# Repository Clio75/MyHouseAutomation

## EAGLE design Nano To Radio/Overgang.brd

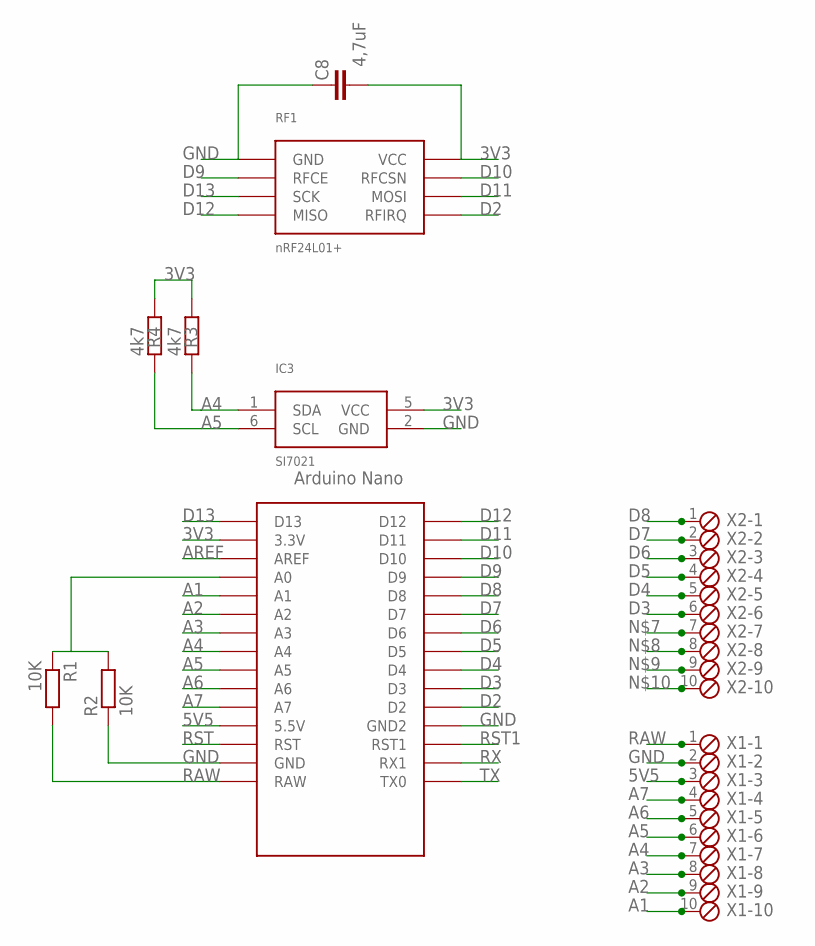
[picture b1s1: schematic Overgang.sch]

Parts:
C8: 4,7uF; C1206K
IC3: SI7021; DFN6
R1, R2: 10K; R0805
R3, R4: 4k7; R0805
RF1: nRF24L01+; 2X4-2.54MM
U$1: NANO
X1, X2: MPT10; 10POL254

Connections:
3V3: C8.1, IC3.5 (VCC), R3.1, R4.1, RF1.P$2 (VCC), U$1.3.3V
5V5: U$1.5V (5.5V), X1.3
A1: U$1.A1, X1.10
A2: U$1.A2, X1.9
A3: U$1.A3, X1.8
A4: IC3.1 (SDA), R3.2, U$1.A4, X1.7
A5: IC3.6 (SCL), R4.2, U$1.A5, X1.6
A6: U$1.A6, X1.5
A7: U$1.A7, X1.4
AREF: U$1.AREF
D2: RF1.P$8 (RFIRQ), U$1.D2
D3: U$1.D3, X2.6
D4: U$1.D4, X2.5
D5: U$1.D5, X2.4
D6: U$1.D6, X2.3
D7: U$1.D7, X2.2
D8: U$1.D8, X2.1
D9: RF1.P$3 (RFCE), U$1.D9
D10: RF1.P$4 (RFCSN), U$1.D10
D11: RF1.P$6 (MOSI), U$1.D11
D12: RF1.P$7 (MISO), U$1.D12
D13: RF1.P$5 (SCK), U$1.D13
GND: C8.2, IC3.2 (GND), R2.1, RF1.P$1 (GND), U$1.GND, U$1.GND1 (GND2), X1.2
unnamed: R1.1, R2.2, U$1.A0
RAW: R1.2, U$1.RAW, X1.1
RST: U$1.RST
RST1: U$1.RST1
RX: U$1.RX1
TX: U$1.TX0

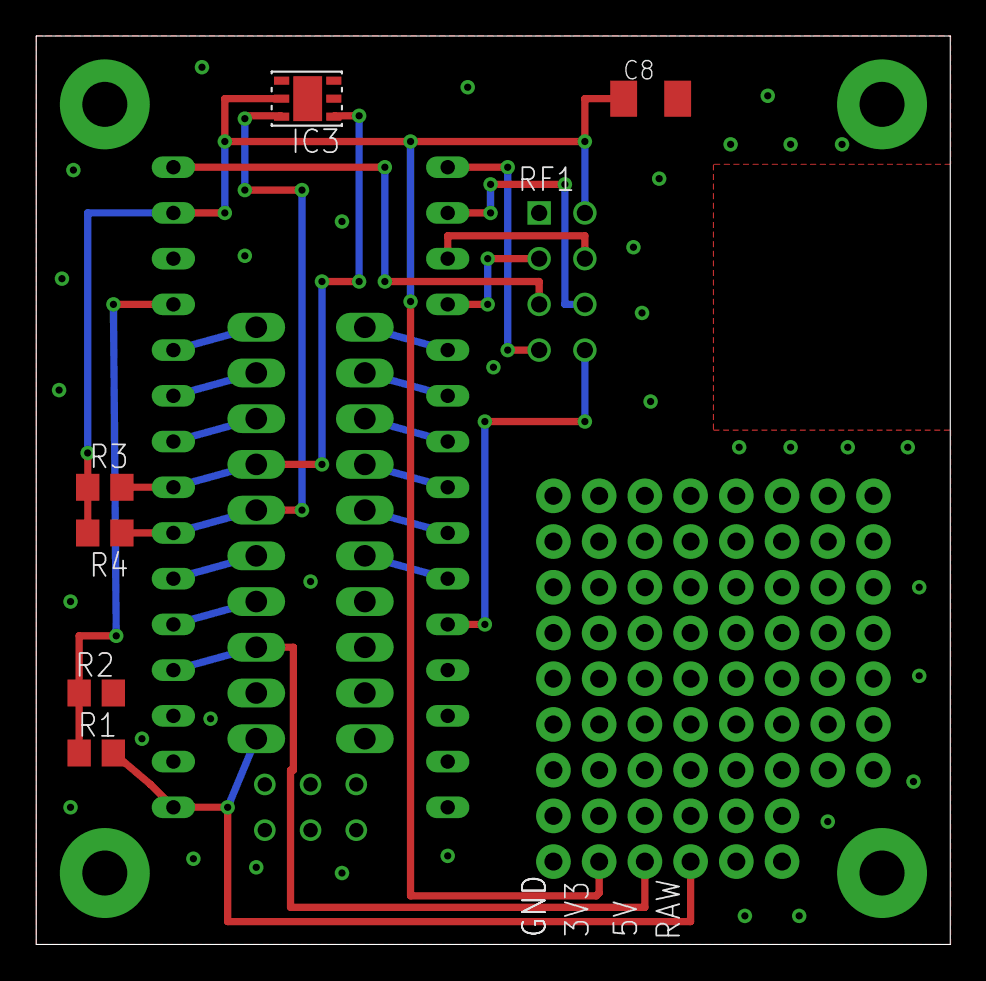
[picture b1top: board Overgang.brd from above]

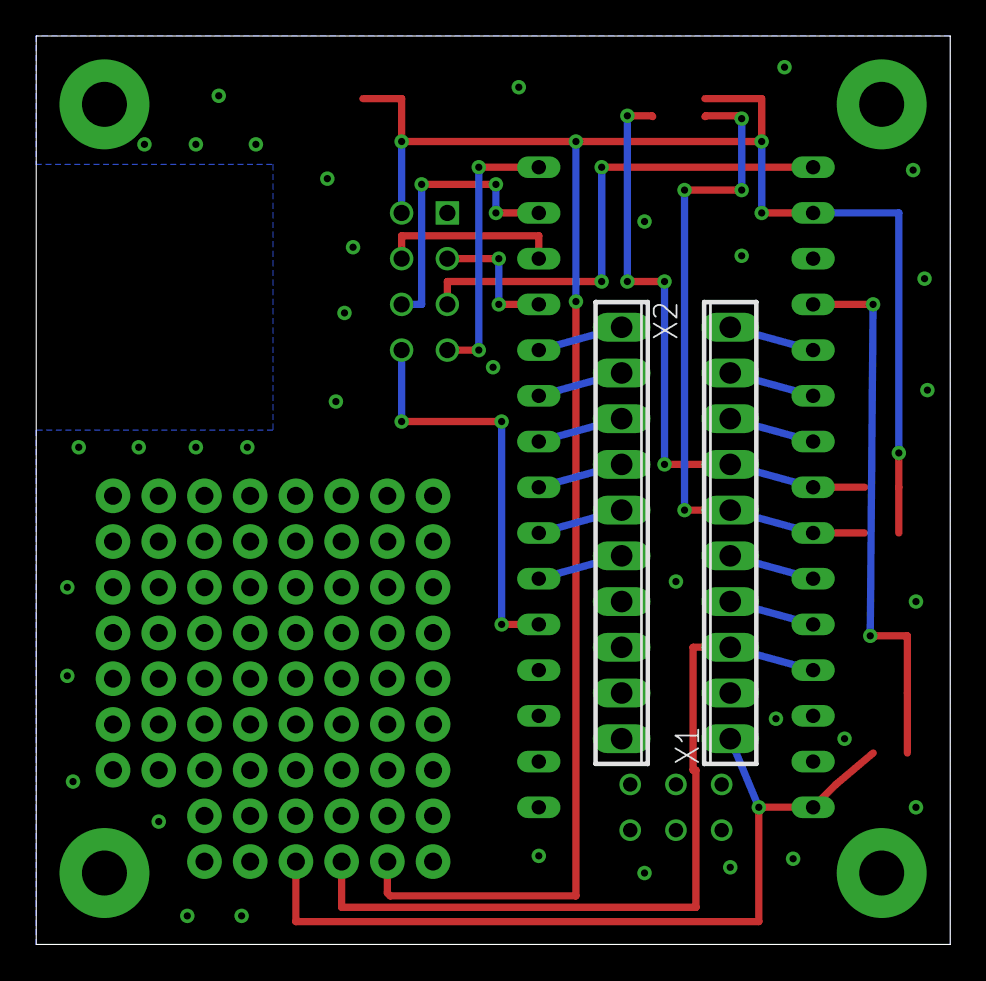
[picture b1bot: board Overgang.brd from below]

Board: 2 copper layers, 50.8 x 50.5 mm, 10 parts (2 on the bottom side), 24 nets.

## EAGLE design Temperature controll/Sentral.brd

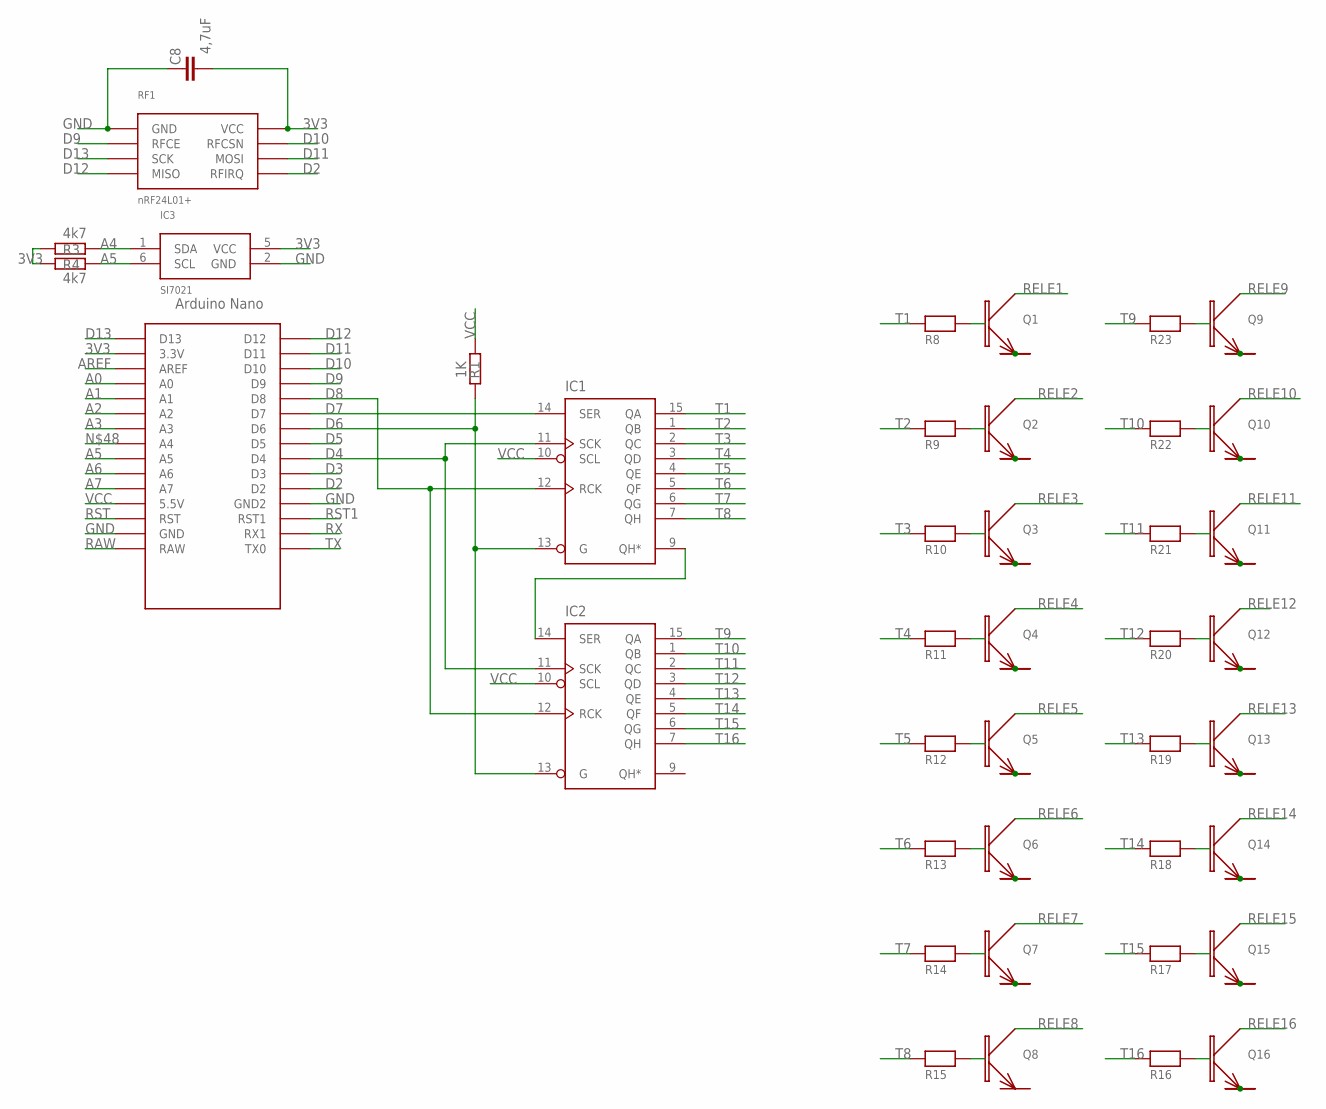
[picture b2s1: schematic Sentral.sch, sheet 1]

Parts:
C8: 4,7uF; C4532
IC1, IC2: 74595; SO-16
IC3: SI7021; DFN6
Q1, Q2, Q3, Q4, Q5, Q6, Q7, Q8, Q9, Q10, Q11, Q12, Q13, Q14, Q15, Q16: BC817; SOT23
R1: 1K; R0805
R3, R4: 4k7; R0805
R8, R9, R10, R11, R12, R13, R14, R15, R16, R17, R18, R19, R20, R21, R22, R23: RES-A; A
RF1: nRF24L01+; 2X4-2.54MM
U$1: NANO

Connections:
3V3: C8.1, IC3.5 (VCC), R3.1, R4.1, RF1.P$2 (VCC), U$1.3.3V; also elsewhere on the board
A0: U$1.A0
A1: U$1.A1
A2: U$1.A2
A3: U$1.A3
A4: IC3.1 (SDA), R3.2
A5: IC3.6 (SCL), R4.2, U$1.A5
A6: U$1.A6
A7: U$1.A7
AREF: U$1.AREF
D2: RF1.P$8 (RFIRQ), U$1.D2
D3: U$1.D3
D4: IC1.11 (SCK), IC2.11 (SCK), U$1.D4
D5: U$1.D5
D6: IC1.13 (G), IC2.13 (G), R1.2, U$1.D6
D7: IC1.14 (SER), U$1.D7
D8: IC1.12 (RCK), IC2.12 (RCK), U$1.D8
D9: RF1.P$3 (RFCE), U$1.D9
D10: RF1.P$4 (RFCSN), U$1.D10
D11: RF1.P$6 (MOSI), U$1.D11
D12: RF1.P$7 (MISO), U$1.D12
D13: RF1.P$5 (SCK), U$1.D13
GND: C8.2, IC1.8 (GND), IC2.8 (GND), IC3.2 (GND), Q1.1 (E), Q2.1 (E), Q3.1 (E), Q4.1 (E), Q5.1 (E), Q6.1 (E), Q7.1 (E), Q8.1 (E), Q9.1 (E), Q10.1 (E), Q11.1 (E), Q12.1 (E), Q13.1 (E), Q14.1 (E), Q15.1 (E), Q16.1 (E), RF1.P$1 (GND), U$1.GND, U$1.GND1 (GND2)
unnamed: Q1.2 (B), R8.2
unnamed: Q2.2 (B), R9.2
unnamed: Q3.2 (B), R10.2
unnamed: Q4.2 (B), R11.2
unnamed: Q5.2 (B), R12.2
unnamed: Q6.2 (B), R13.2
unnamed: Q7.2 (B), R14.2
unnamed: Q8.2 (B), R15.2
unnamed: IC1.9 (QH*), IC2.14 (SER)
unnamed: Q16.2 (B), R16.2
unnamed: Q15.2 (B), R17.2
unnamed: Q14.2 (B), R18.2
unnamed: Q13.2 (B), R19.2
unnamed: Q12.2 (B), R20.2
unnamed: Q11.2 (B), R21.2
unnamed: Q10.2 (B), R22.2
unnamed: Q9.2 (B), R23.2
RAW: U$1.RAW
RELE1: Q1.3 (C); also elsewhere on the board
RELE2: Q2.3 (C); also elsewhere on the board
RELE3: Q3.3 (C); also elsewhere on the board
RELE4: Q4.3 (C); also elsewhere on the board
RELE5: Q5.3 (C); also elsewhere on the board
RELE6: Q6.3 (C); also elsewhere on the board
RELE7: Q7.3 (C); also elsewhere on the board
RELE8: Q8.3 (C); also elsewhere on the board
RELE9: Q9.3 (C); also elsewhere on the board
RELE10: Q10.3 (C); also elsewhere on the board
RELE11: Q11.3 (C); also elsewhere on the board
RELE12: Q12.3 (C); also elsewhere on the board
RELE13: Q13.3 (C); also elsewhere on the board
RELE14: Q14.3 (C); also elsewhere on the board
RELE15: Q15.3 (C); also elsewhere on the board
RELE16: Q16.3 (C); also elsewhere on the board
RST: U$1.RST
RST1: U$1.RST1
RX: U$1.RX1
T1: IC1.15 (QA), R8.1
T2: IC1.1 (QB), R9.1
T3: IC1.2 (QC), R10.1
T4: IC1.3 (QD), R11.1
T5: IC1.4 (QE), R12.1
T6: IC1.5 (QF), R13.1
T7: IC1.6 (QG), R14.1
T8: IC1.7 (QH), R15.1
T9: IC2.15 (QA), R23.1
T10: IC2.1 (QB), R22.1
T11: IC2.2 (QC), R21.1
T12: IC2.3 (QD), R20.1
T13: IC2.4 (QE), R19.1
T14: IC2.5 (QF), R18.1
T15: IC2.6 (QG), R17.1
T16: IC2.7 (QH), R16.1
TX: U$1.TX0
VCC: IC1.10 (SCL), IC1.16 (VCC), IC2.10 (SCL), IC2.16 (VCC), R1.1, U$1.5V (5.5V)

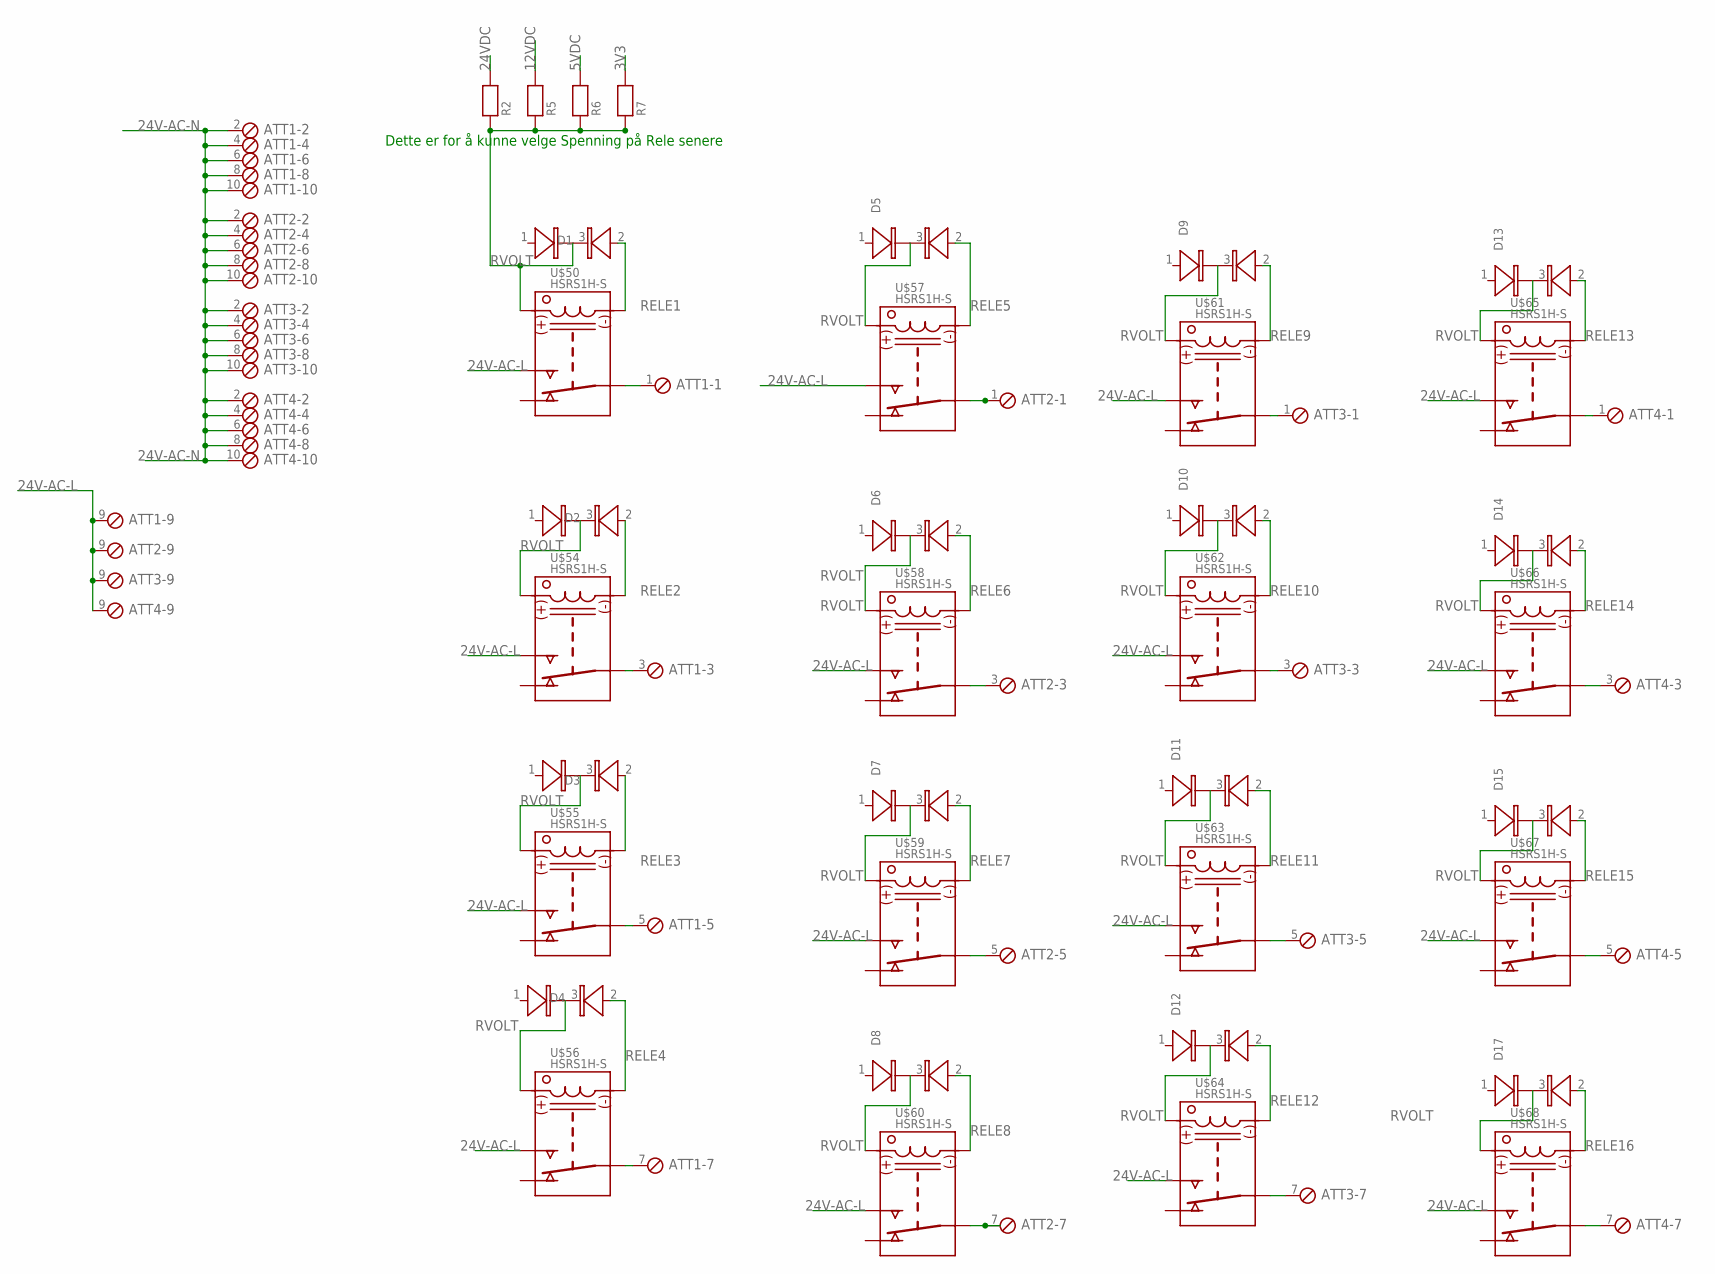
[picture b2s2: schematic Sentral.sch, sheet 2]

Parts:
ATT1, ATT2, ATT3, ATT4: MPT10; 10POL254
D1, D2, D3, D4, D5, D6, D7, D8, D9, D10, D11, D12, D13, D14, D15, D17: BAV70; SOT23
R2, R5, R6, R7: RES-C; C
U$50, U$54, U$55, U$56, U$57, U$58, U$59, U$60, U$61, U$62, U$63, U$64, U$65, U$66, U$67, U$68: HSRS1H-S; DIL12RLY

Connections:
3V3: R7.2; also elsewhere on the board
5VDC: R6.2
12VDC: R5.2
24V-AC-L: ATT1.9, ATT2.9, ATT3.9, ATT4.9, U$50.1, U$54.1, U$55.1, U$56.1, U$57.1, U$58.1, U$59.1, U$60.1, U$61.1, U$62.1, U$63.1, U$64.1, U$65.1, U$66.1, U$67.1, U$68.1
24V-AC-N: ATT1.2, ATT1.4, ATT1.6, ATT1.8, ATT1.10, ATT2.2, ATT2.4, ATT2.6, ATT2.8, ATT2.10, ATT3.2, ATT3.4, ATT3.6, ATT3.8, ATT3.10, ATT4.2, ATT4.4, ATT4.6, ATT4.8, ATT4.10
24VDC: R2.2
unnamed: ATT2.1, U$57.6 (6,7), U$57.7 (6,7)
unnamed: ATT2.3, U$58.6 (6,7), U$58.7 (6,7)
unnamed: ATT2.5, U$59.6 (6,7), U$59.7 (6,7)
unnamed: ATT2.7, U$60.6 (6,7), U$60.7 (6,7)
unnamed: ATT1.1, U$50.6 (6,7), U$50.7 (6,7)
unnamed: ATT1.3, U$54.6 (6,7), U$54.7 (6,7)
unnamed: ATT1.5, U$55.6 (6,7), U$55.7 (6,7)
unnamed: ATT3.7, U$64.6 (6,7), U$64.7 (6,7)
unnamed: ATT4.1, U$65.6 (6,7), U$65.7 (6,7)
unnamed: ATT3.5, U$63.6 (6,7), U$63.7 (6,7)
unnamed: ATT3.3, U$62.6 (6,7), U$62.7 (6,7)
unnamed: ATT3.1, U$61.6 (6,7), U$61.7 (6,7)
unnamed: ATT4.3, U$66.6 (6,7), U$66.7 (6,7)
unnamed: ATT4.5, U$67.6 (6,7), U$67.7 (6,7)
unnamed: ATT4.7, U$68.6 (6,7), U$68.7 (6,7)
unnamed: ATT1.7, U$56.6 (6,7), U$56.7 (6,7)
RELE1: D1.2 (A2), U$50.11; also elsewhere on the board
RELE2: D2.2 (A2), U$54.11; also elsewhere on the board
RELE3: D3.2 (A2), U$55.11; also elsewhere on the board
RELE4: D4.2 (A2), U$56.11; also elsewhere on the board
RELE5: D5.2 (A2), U$57.11; also elsewhere on the board
RELE6: D6.2 (A2), U$58.11; also elsewhere on the board
RELE7: D7.2 (A2), U$59.11; also elsewhere on the board
RELE8: D8.2 (A2), U$60.11; also elsewhere on the board
RELE9: D9.2 (A2), U$61.11; also elsewhere on the board
RELE10: D10.2 (A2), U$62.11; also elsewhere on the board
RELE11: D11.2 (A2), U$63.11; also elsewhere on the board
RELE12: D12.2 (A2), U$64.11; also elsewhere on the board
RELE13: D13.2 (A2), U$65.11; also elsewhere on the board
RELE14: D14.2 (A2), U$66.11; also elsewhere on the board
RELE15: D15.2 (A2), U$67.11; also elsewhere on the board
RELE16: D17.2 (A2), U$68.11; also elsewhere on the board
RVOLT: D1.3 (K), D2.3 (K), D3.3 (K), D4.3 (K), D5.3 (K), D6.3 (K), D7.3 (K), D8.3 (K), D9.3 (K), D10.3 (K), D11.3 (K), D12.3 (K), D13.3 (K), D14.3 (K), D15.3 (K), D17.3 (K), R2.1, R5.1, R6.1, R7.1, U$50.2, U$54.2, U$55.2, U$56.2, U$57.2, U$58.2, U$59.2, U$60.2, U$61.2, U$62.2, U$63.2, U$64.2, U$65.2, U$66.2, U$67.2, U$68.2

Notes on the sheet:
Dette er for å kunne velge Spenning på Rele senere

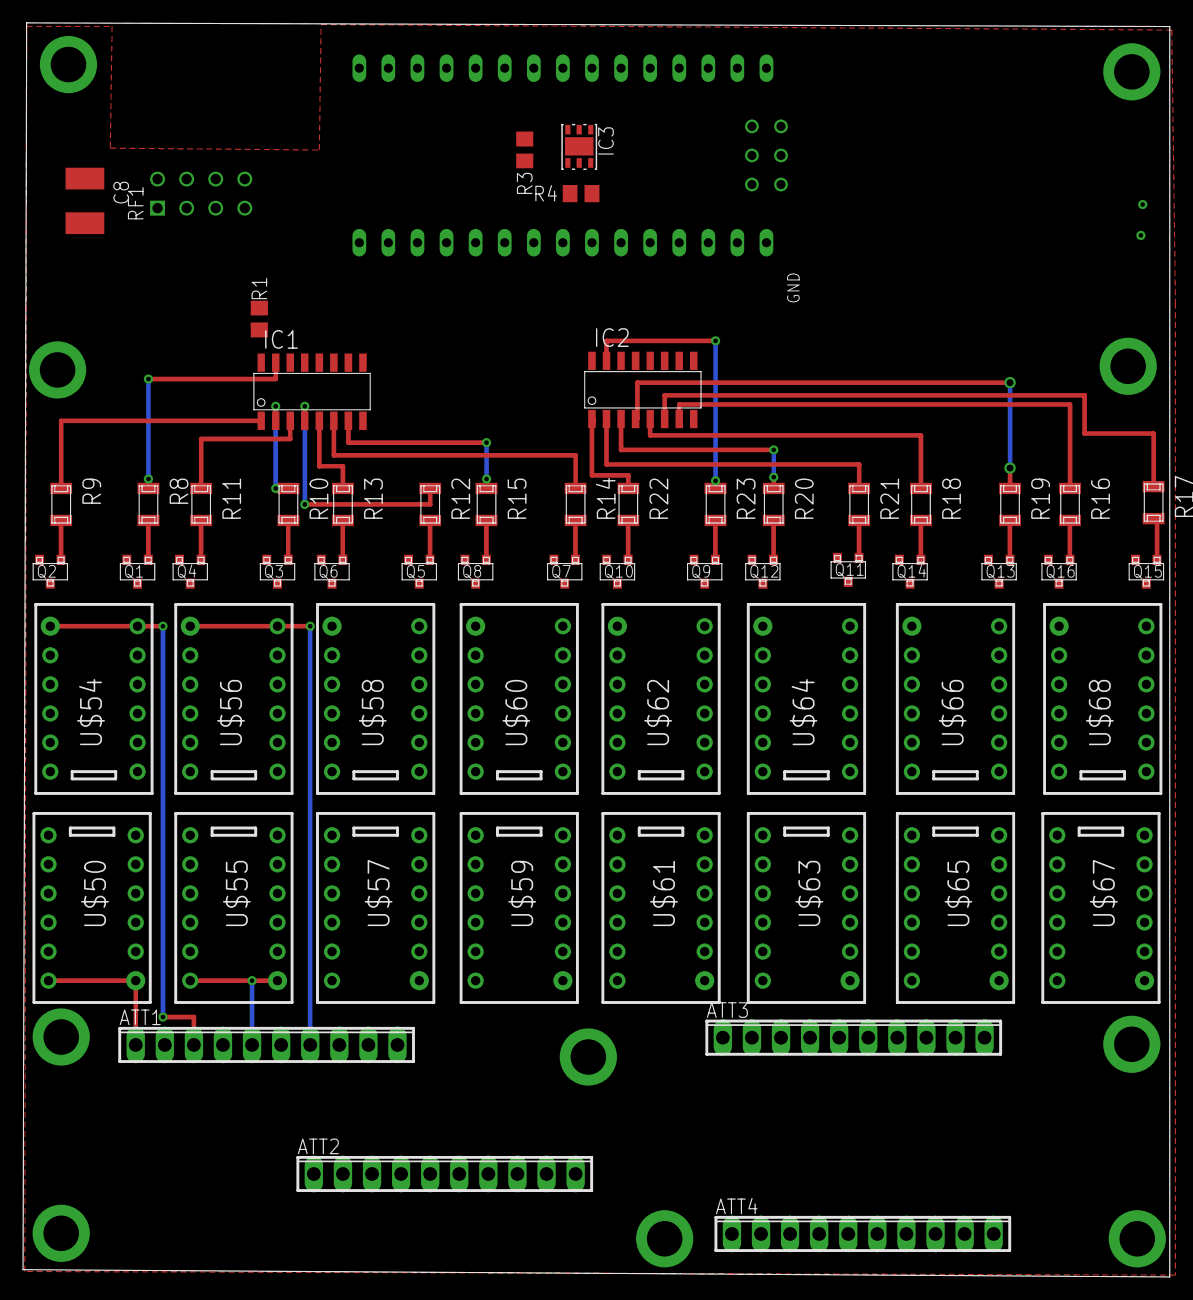
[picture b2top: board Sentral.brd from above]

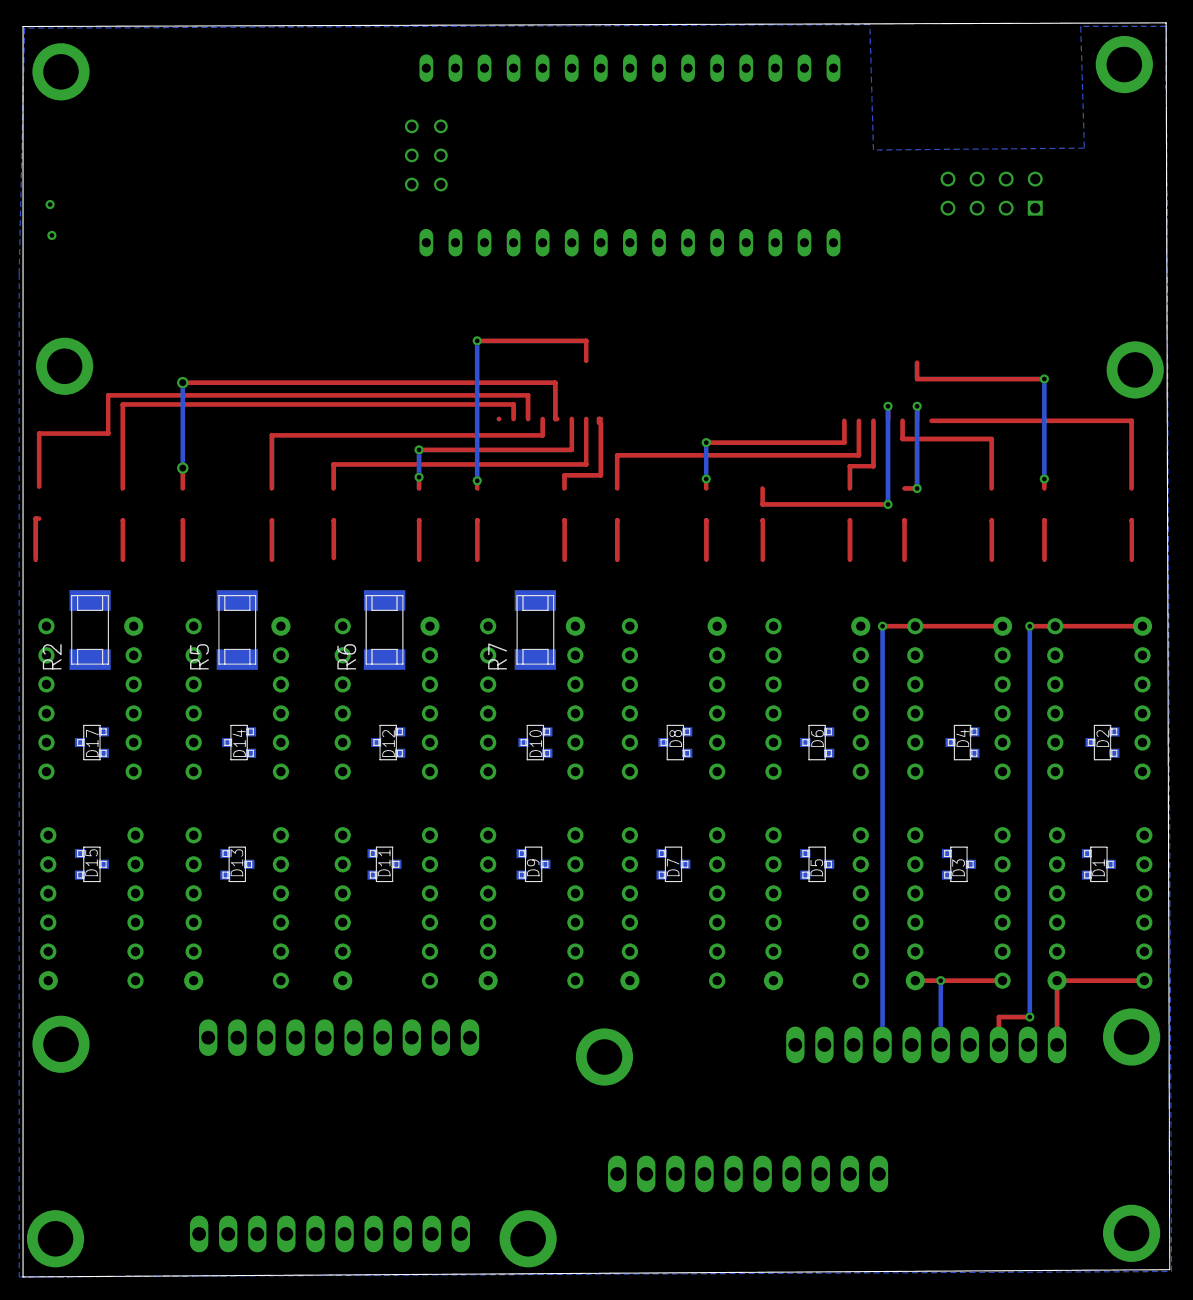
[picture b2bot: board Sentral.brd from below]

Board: 2 copper layers, 100.2 x 109.5 mm, 81 parts (20 on the bottom side), 83 nets.

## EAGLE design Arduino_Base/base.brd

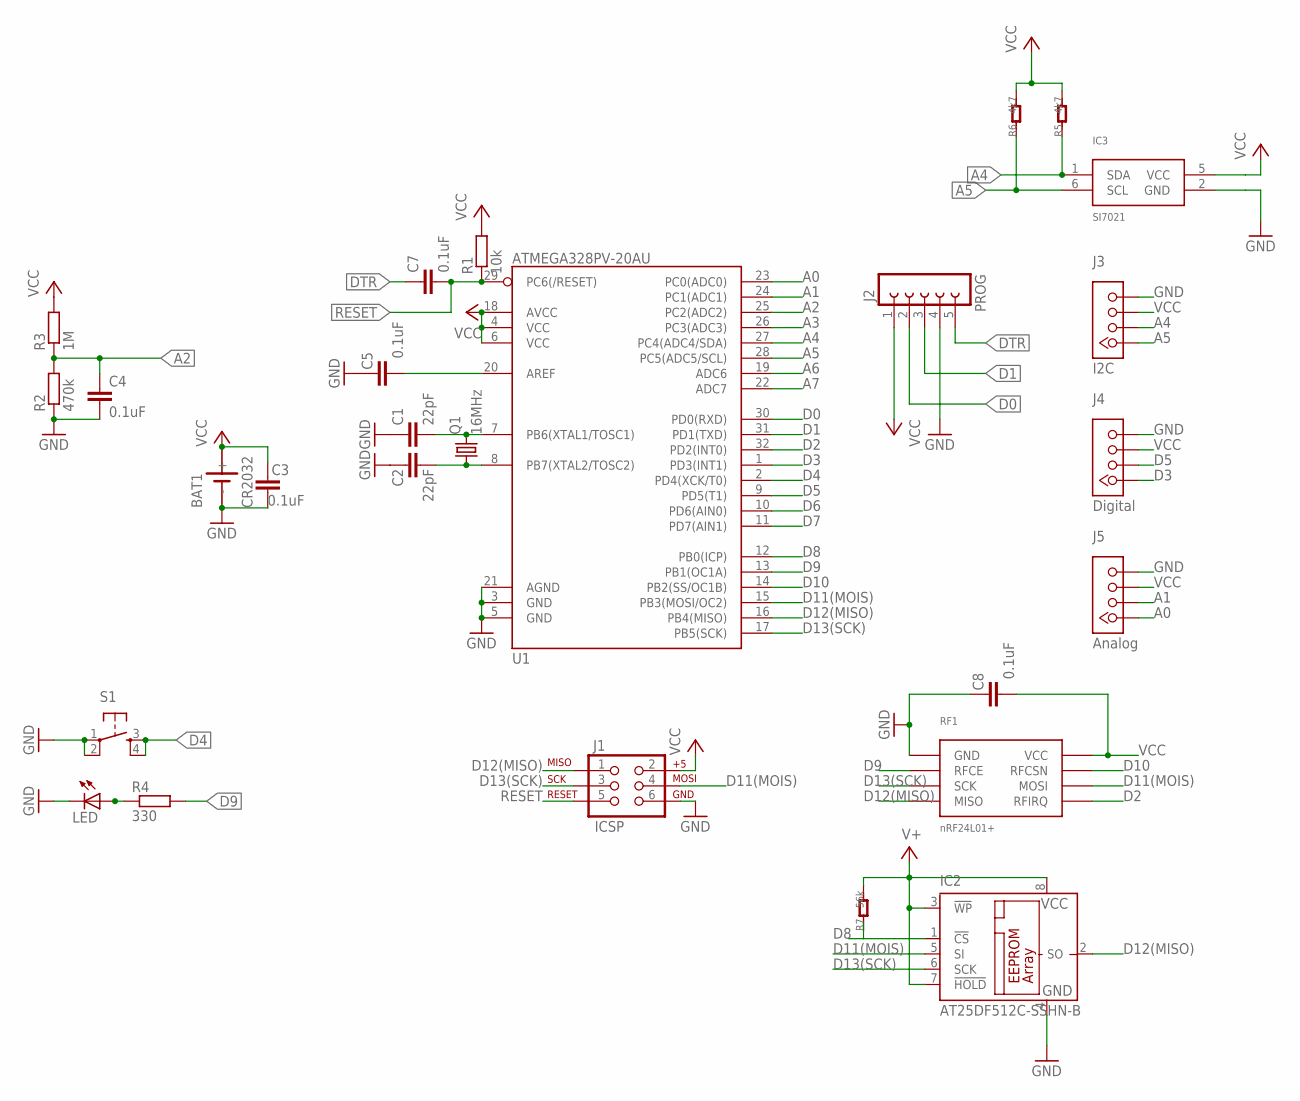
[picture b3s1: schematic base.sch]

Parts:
BAT1: CR2032; SN2032
C1, C2: 22pF; C0805
C3, C4, C5, C7, C8: 0.1uF; C0805
IC2: AT25DF512C-SSHN-B; SO-08
IC3: SI7021; DFN6
J1: ICSP; 2X3-NS
J3: I2C; TWIG-4P-2.0
J4: Digital; TWIG-4P-2.0
J5: Analog; TWIG-4P-2.0
LED: LEDCHIP-LED0805; CHIP-LED0805
PROG: J2; FE05-1
Q1: 16MHz; CTS406
R1: 10k; R0805
R2: 470k; R0805
R3: 1M; R0805
R4: 330; R0805
R5, R6: 4k7; R0402
R7: 56k; R0402
RF1: nRF24L01+; 2X4-2.54MM
S1: TAC_SWITCHPTH; TACTILE-PTH
U1: ATMEGA328PV-20AU; TQFP32-08

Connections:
A0: J5.P$1, U1.23 (PC0(ADC0))
A1: J5.P$2, U1.24 (PC1(ADC1))
A2: C4.1, R2.2, R3.1, U1.25 (PC2(ADC2))
A3: U1.26 (PC3(ADC3))
A4: IC3.1 (SDA), J3.P$2, R5.1, U1.27 (PC4(ADC4/SDA))
A5: IC3.6 (SCL), J3.P$1, R6.1, U1.28 (PC5(ADC5/SCL))
A6: U1.19 (ADC6)
A7: U1.22 (ADC7)
D0: PROG.2, U1.30 (PD0(RXD))
D1: PROG.3, U1.31 (PD1(TXD))
D2: RF1.P$8 (RFIRQ), U1.32 (PD2(INT0))
D3: J4.P$1, U1.1 (PD3(INT1))
D4: S1.3, S1.4, U1.2 (PD4(XCK/T0))
D5: J4.P$2, U1.9 (PD5(T1))
D6: U1.10 (PD6(AIN0))
D7: U1.11 (PD7(AIN1))
D8: IC2.1 (!CS), U1.12 (PB0(ICP))
D9: R4.2, RF1.P$3 (RFCE), U1.13 (PB1(OC1A))
D10: RF1.P$4 (RFCSN), U1.14 (PB2(SS/OC1B))
D11(MOIS): IC2.5 (SI), J1.4, RF1.P$6 (MOSI), U1.15 (PB3(MOSI/OC2))
D12(MISO): IC2.2 (SO), J1.1, RF1.P$7 (MISO), U1.16 (PB4(MISO))
D13(SCK): IC2.6 (SCK), J1.3, RF1.P$5 (SCK), U1.17 (PB5(SCK))
DTR: C7.1, PROG.5
GND: BAT1.-, C1.1, C2.1, C3.1, C4.2, C5.2, C8.2, IC2.4 (GND), IC3.2 (GND), J1.6, J3.P$4, J4.P$4, J5.P$4, LED.C, PROG.4, R2.1, RF1.P$1 (GND), S1.1, S1.2, U1.3 (GND), U1.5 (GND), U1.21 (AGND)
unnamed: C1.2, Q1.3 (2), U1.7 (PB6(XTAL1/TOSC1))
unnamed: C2.2, Q1.1, U1.8 (PB7(XTAL2/TOSC2))
unnamed: C5.1, U1.20 (AREF)
unnamed: LED.A, R4.1
RESET: C7.2, J1.5, R1.1, U1.29 (PC6(/RESET))
VCC: BAT1.+, C3.2, C8.1, IC2.3 (!WP), IC2.7 (!HOLD), IC2.8 (VCC), IC3.5 (VCC), J1.2, J3.P$3, J4.P$3, J5.P$3, PROG.1, R1.2, R3.2, R5.2, R6.2, R7.2, RF1.P$2 (VCC), U1.4 (VCC), U1.6 (VCC), U1.18 (AVCC)

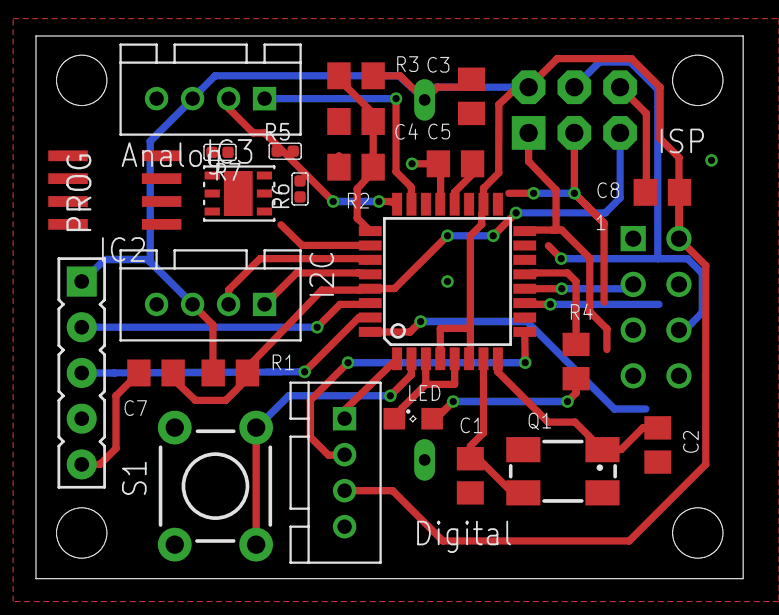
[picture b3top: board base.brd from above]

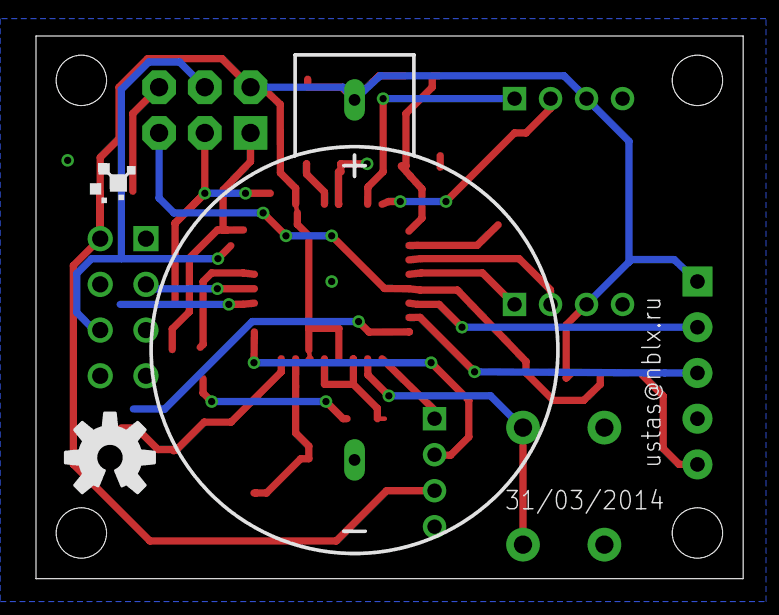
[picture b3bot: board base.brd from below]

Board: 2 copper layers, 39.3 x 30.2 mm, 28 parts (2 on the bottom side), 25 nets.

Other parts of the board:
E$1: OSHW-LOGO-M

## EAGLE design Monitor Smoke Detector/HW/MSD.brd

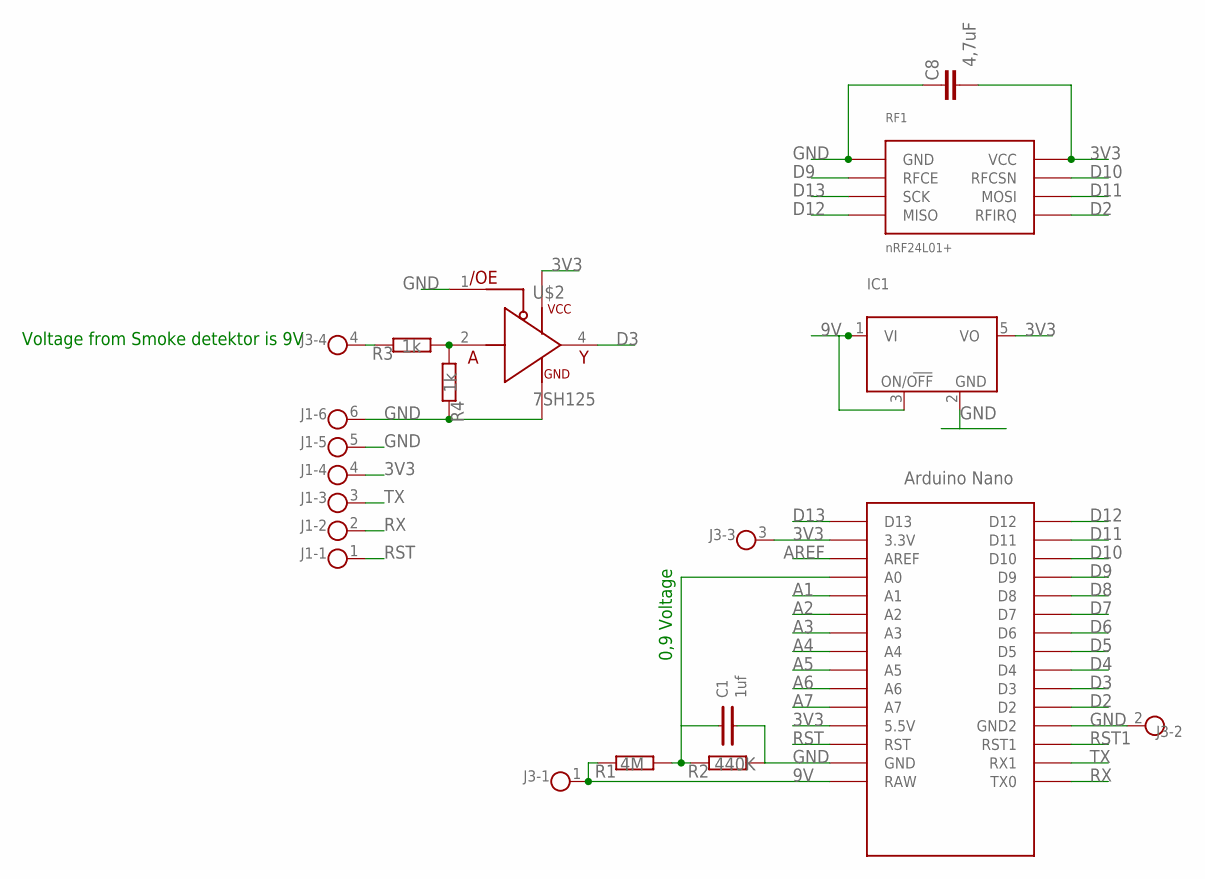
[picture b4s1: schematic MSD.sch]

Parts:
C1: 1uf; 0805
C8: 4,7uF; C1206K
IC1: LP2980IM5; SOT23-5
J1: FTDI; LIST6B
J3: LIST4
R1: 4M; R0805
R2: 440K; R0805
R3, R4: 1k; R0805
RF1: nRF24L01+; 2X4-2.54MM
U$1: NANO
U$2: 7SH125; SOT23

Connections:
3V3: C8.1, IC1.5 (VO), J1.4, J3.3, RF1.P$2 (VCC), U$1.3.3V, U$1.5V (5.5V), U$2.5 (VCC)
9V: IC1.1 (VI), IC1.3 (ON/OFF), J3.1, R1.2, U$1.RAW
A1: U$1.A1
A2: U$1.A2
A3: U$1.A3
A4: U$1.A4
A5: U$1.A5
A6: U$1.A6
A7: U$1.A7
AREF: U$1.AREF
D2: RF1.P$8 (RFIRQ), U$1.D2
D3: U$1.D3, U$2.4 (OUT)
D4: U$1.D4
D5: U$1.D5
D6: U$1.D6
D7: U$1.D7
D8: U$1.D8
D9: RF1.P$3 (RFCE), U$1.D9
D10: RF1.P$4 (RFCSN), U$1.D10
D11: RF1.P$6 (MOSI), U$1.D11
D12: RF1.P$7 (MISO), U$1.D12
D13: RF1.P$5 (SCK), U$1.D13
GND: C1.2, C8.2, IC1.2 (GND), J1.5, J1.6, J3.2, R2.1, R4.2, RF1.P$1 (GND), U$1.GND, U$1.GND1 (GND2), U$2.1 (/OE), U$2.3 (GND)
unnamed: J3.4, R3.2
unnamed: C1.1, R1.1, R2.2, U$1.A0
unnamed: R3.1, R4.1, U$2.2 (A)
RST: J1.1, U$1.RST
RST1: U$1.RST1
RX: J1.2, U$1.TX0
TX: J1.3, U$1.RX1

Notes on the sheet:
0,9 Voltage
Voltage from Smoke detektor is 9V

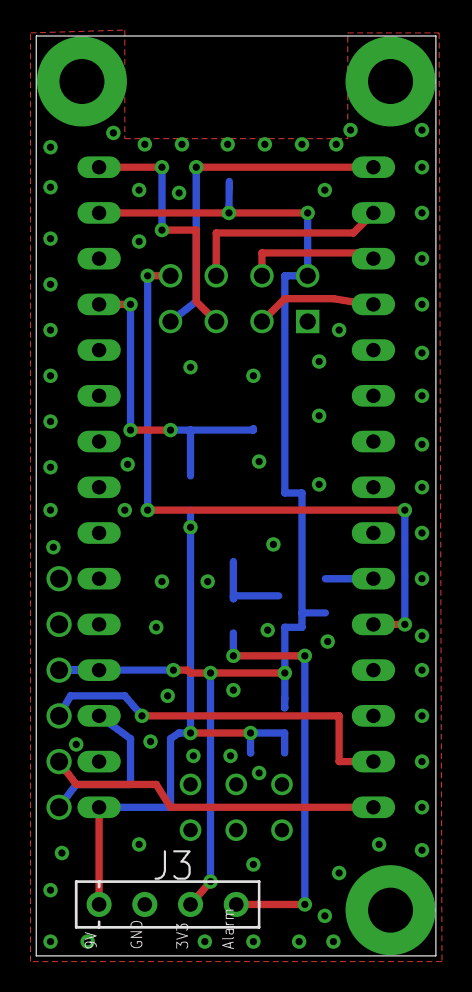
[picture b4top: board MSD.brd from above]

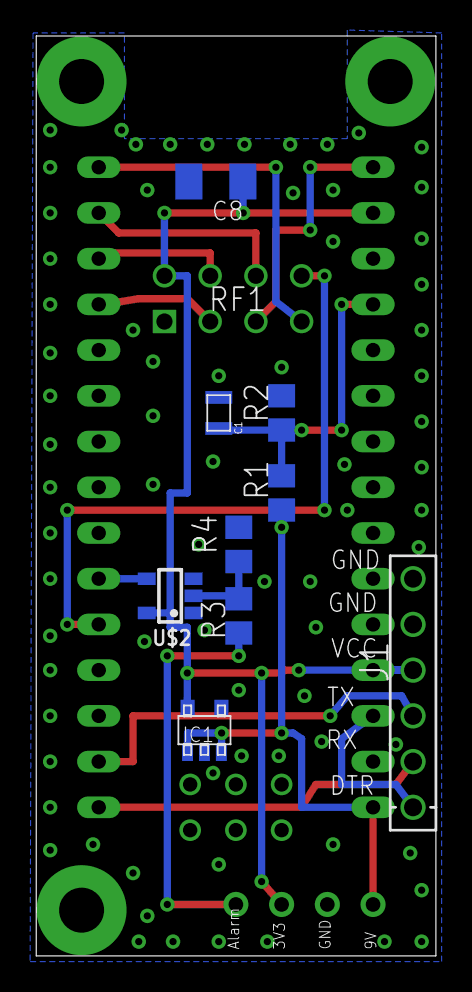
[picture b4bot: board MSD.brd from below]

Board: 2 copper layers, 22.2 x 51.1 mm, 12 parts (10 on the bottom side), 16 nets.

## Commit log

2016-11-02 Adding to GIT
2018-08-27 Adding

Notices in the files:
parts and their libraries:
SparkFun-DigitalIC: Licensing: CC v3.0 Share-Alike You are welcome to use this library for commercial purposes.
7sh: Copyright (C) 2005 by Bob Starr, rtzaudio@mindspring.com
